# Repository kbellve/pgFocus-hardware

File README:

View this project on [CADLAB.io](https://cadlab.io/project/1071). 

pgFocus stands for Pretty Good Focus. It isn't "Definite" Focus nor "Perfect" Focus, but it is Pretty Good.  

pgFocus is fully compatible with uManager.

	1) Open Source Software

	2) Open Hardware

	3) Reasonably Fast
		pgFocus runs at 30Hz

	4) Reasonably inexpensive

	5) Independent of image capture
		In primary mode, pgFocus is asynchronous of uManager.

	6) uManager will be able to set, confirm or change focus positions through a uManager device adapter.

	7) Designed to work with a piezo Z controller for fastest response, but could be used to indirectly drive a motorized Z-Drive via a uManager device adapter.

	8) 3D Focus Stabilization
		Most focus stabilization devices turn off during 3D image capture, unlike pgFocus.

	9) Focus stability reporting
		You will quickly learn what disturbs your microscope and how to minimize those disturbances.

The pgFocus hardware, including all the files required to produce the hardware, is licensed under a Creative Commons Attribution-ShareAlike 4.0 International License.

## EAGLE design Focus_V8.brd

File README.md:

pgFocus
=======

Focus Stabilization

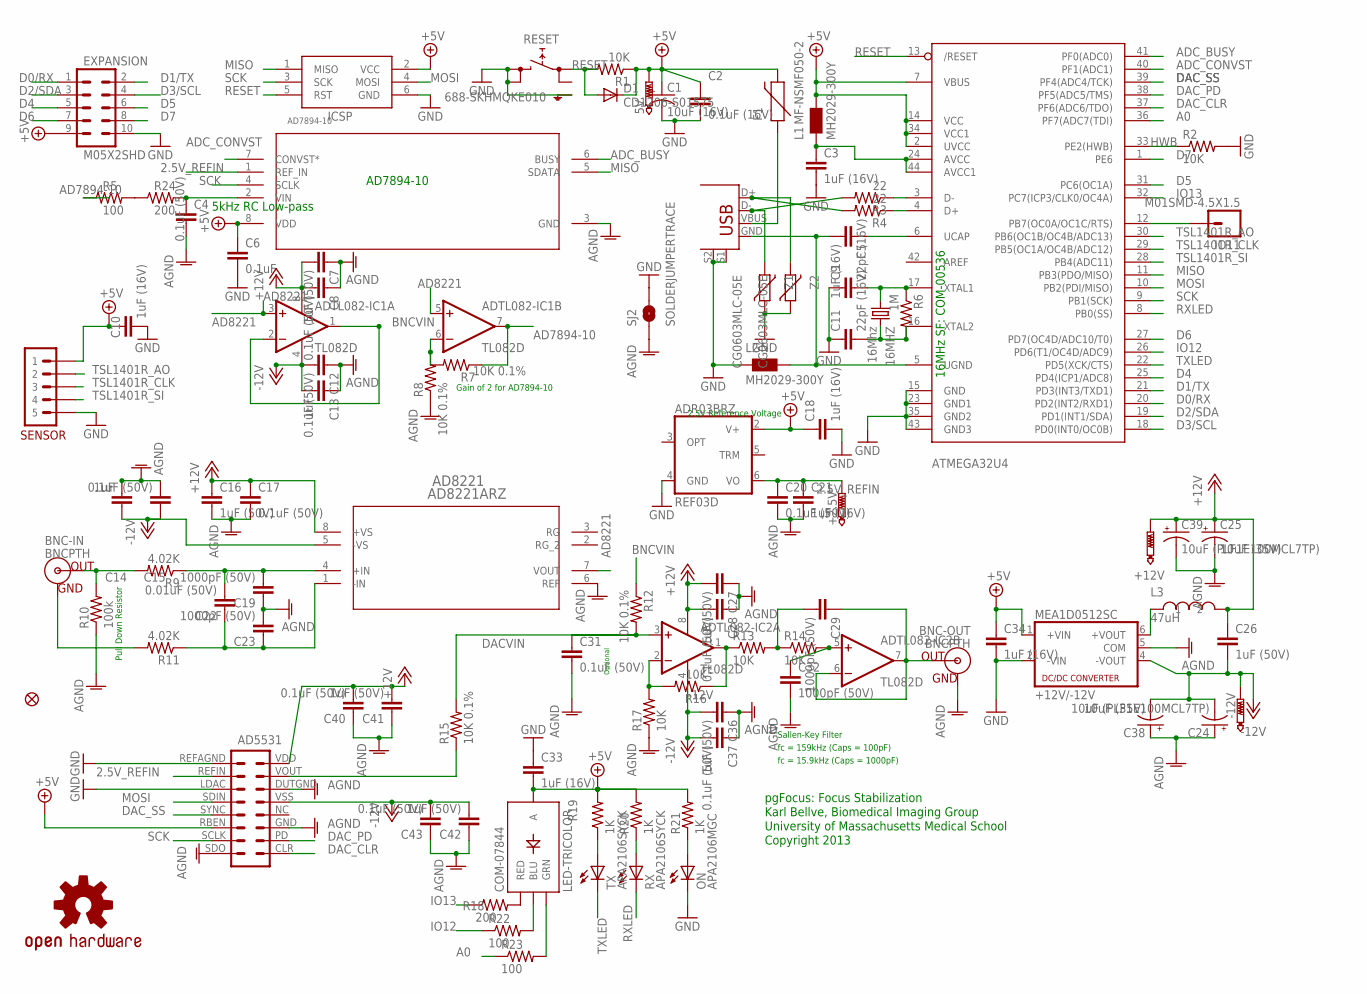
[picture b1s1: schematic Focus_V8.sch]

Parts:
5V: PTR1TP20R; TP20R
16MHZ: 16Mhz; HC49U-V
+2.5V, +12V: PTR1TP20R; TP20R
-12V: PTR1TP20R; TP20R
AD7894-10: AD7894ARZ-10; R_8
AD8221: AD8221ARZ; R_8
ADR03BRZ: REF03D; SO08
ADTL082-IC1, ADTL082-IC2: TL082D; SO08
ATMEGA32U4: ATMEGA32U4-AU; TQFP44
BNC-IN: BNCPTH; BNC
BNC-OUT: BNCPTH; BNC
C1: 10uF (16V); EIA3216-KIT
C2: 0.1uF (16V); 0603-CAP
C3, C5, C10, C18, C21, C33, C34: 1uF (16V); 0603-CAP
C4, C8, C12, C15, C17, C20, C28, C31, C37, C40, C43: 0.1uF (50V); 0603-CAP
C6: 0.1uF; 0603-CAP
C7, C16, C26, C27, C36, C41, C42: 1uF (50V); 0603-CAP
C9, C11: 22pF (16V); 0603-CAP
C13, C14: 1uF; 0603-CAP
C19, C23, C29, C32: 1000pF (50V); 0603-CAP
C22: 0.01uF (50V); 0603-CAP
C24, C39: 10uF (PLF1E100MCL7TP); CPOL-RADIAL-100UF-25V
C25, C38: 10uF (35V); EIA3216-KIT
COM-07844: LED-TRICOLOR; LED-TRICOLOR-SMD
D1: CD1206-S01575; MINIMELF
EXPANSION: M05X2SHD; 2X5-SHROUDED
F1: MF-NSMF050-2; PTC-1206
ICSP: AVRISP-6; AVRISP
IO11: M01SMD-4.5X1.5; PAD-1.5X4.5
JP1: FIDUCIAL1.5X3; FIDUCIAL-1.5X3
L1, L2: MH2029-300Y; 0805
L3: 47uH; 11R473C
MEA1D0512SC: +12V/-12V; NMA
ON: APA2106MGC; CHIPLED_0805
R1, R2, R13, R14, R16, R17: 10K; 0603-RES
R3, R4: 22; 0603-RES
R5, R22, R23: 100; 0603-RES
R6: 1M; 0603-RES
R7, R8, R12, R15: 10K 0.1%; 0603-RES
R9, R11: 4.02K; 0603-RES
R10: 100k; 0603-RES
R18, R24: 200; 0603-RES
R19, R20, R21: 1K; 0603-RES
RESET: 688-SKHMQKE010; SKHMPXE010
RX: APA2106SYCK; CHIPLED_0805
SENSOR: M05; M05JST-PTH
SJ2: SOLDERJUMPERTRACE; SJ_2S-TRACE
TX: APA2106SYCK; CHIPLED_0805
U$1: AD5531
U$3: OSHW-LOGOL; OSHW-LOGO-L
USB: USB+SHIELD; USB-B-PTH
Z1, Z2: CG0603MLC-05E; CT/CN0603

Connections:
2.5V_REFIN: +2.5V.TP, AD7894-10.1 (REF_IN), ADR03BRZ.6 (VO), C20.1, C21.1, U$1.REFIN
+5V: 5V.TP, AD7894-10.8 (VDD), ADR03BRZ.2 (V+), ATMEGA32U4.2 (UVCC), ATMEGA32U4.7 (VBUS), ATMEGA32U4.14 (VCC), ATMEGA32U4.34 (VCC1), C1.A (+), C2.1, C6.1, C10.1, C18.1, C33.2, C34.1, COM-07844.A, D1.C, EXPANSION.9, F1.2, ICSP.2 (VCC), L1.2, MEA1D0512SC.1 (+VIN), R1.1, R19.2, R20.2, R21.2, SENSOR.P$1 (1), U$1.RBEN
+12V: +12V.TP, AD8221.8 (+VS), ADTL082-IC1.8 (V+), ADTL082-IC2.8 (V+), C7.2, C8.2, C16.1, C17.1, C25.A (+), C26.1, C27.2, C28.2, C39.1 (+), C40.2, C41.2, L3.P$2 (2), U$1.VDD
-12V: -12V.TP, AD8221.5 (-VS), ADTL082-IC1.4 (V-), ADTL082-IC2.4 (V-), C12.2, C13.2, C14.1, C15.1, C24.2 (-), C26.2, C36.2, C37.2, C38.C (-), C42.2, C43.2, MEA1D0512SC.4 (-VOUT), U$1.VSS
A0: ATMEGA32U4.36 (PF7(ADC7(TDI)), R23.1
AD7894-10: ADTL082-IC1.7 (OUT), R5.1, R7.1
AD8221: AD8221.7 (VOUT), ADTL082-IC1.3 (+IN), ADTL082-IC1.5 (+IN)
ADC_BUSY: AD7894-10.6 (BUSY), ATMEGA32U4.41 (PF0(ADC0))
ADC_CONVST: AD7894-10.7 (CONVST*), ATMEGA32U4.40 (PF1(ADC1))
AGND: AD7894-10.3 (GND), AD8221.6 (REF), BNC-OUT.GND, C4.2, C7.1, C8.1, C12.1, C13.1, C14.2, C15.2, C16.2, C17.2, C19.1, C20.2, C21.2, C23.2, C24.1 (+), C25.C (-), C27.1, C28.1, C31.2, C32.2, C36.1, C37.1, C38.A (+), C39.2 (-), C40.1, C41.1, C42.1, C43.1, MEA1D0512SC.5 (COM), R8.1, R10.1, R17.1, SJ2.1, U$1.DUTGND, U$1.GND, U$1.SDO
BNCVIN: ADTL082-IC1.1 (OUT), ADTL082-IC1.2 (-IN), R12.1
D0/RX: ATMEGA32U4.20 (PD2(INT2/RXD1)), EXPANSION.1
D1/TX: ATMEGA32U4.21 (PD3(INT3/TXD1)), EXPANSION.2
D2/SDA: ATMEGA32U4.19 (PD1(INT1/SDA)), EXPANSION.3
D3/SCL: ATMEGA32U4.18 (PD0(INT0/OC0B)), EXPANSION.4
D4: ATMEGA32U4.25 (PD4(ICP1/ADC8)), EXPANSION.5
D5: ATMEGA32U4.31 (PC6(OC1A)), EXPANSION.6
D6: ATMEGA32U4.27 (PD7(OC4D/ADC10/T0)), EXPANSION.7
D7: ATMEGA32U4.1 (PE6), EXPANSION.8
DACVIN: ADTL082-IC2.3 (+IN), C31.1, R12.2, R15.2
DAC_CLR: ATMEGA32U4.37 (PF6(ADC6/TDO)), U$1.CLR
DAC_PD: ATMEGA32U4.38 (PF5(ADC5/TMS)), U$1.PD
DAC_SS: ATMEGA32U4.39 (PF4(ADC4/TCK)), U$1.SYNC
GND: ADR03BRZ.4 (GND), ATMEGA32U4.15 (GND), ATMEGA32U4.23 (GND1), ATMEGA32U4.35 (GND2), ATMEGA32U4.43 (GND3), C1.C (-), C2.2, C3.2, C6.2, C9.1, C10.2, C11.1, C18.2, C33.1, C34.2, EXPANSION.10, ICSP.6 (GND), L2.1, MEA1D0512SC.2 (-VIN), ON.CATHODE (C), R2.2, RESET.3 (2.1), RESET.4 (2.2), RESET.5 (SH), SENSOR.P$5 (5), SJ2.2, U$1.LDAC, U$1.REFAGND, USB.S1, USB.S2, Z1.1, Z2.1
HWB: ATMEGA32U4.33 (PE2(HWB)), R2.1
IO12: ATMEGA32U4.26 (PD6(T1/OC4D/ADC9)), R22.1
IO13: ATMEGA32U4.32 (PC7(ICP3/CLK0/OC4A)), R18.1
MISO: AD7894-10.5 (SDATA), ATMEGA32U4.11 (PB3(PDO/MISO)), ICSP.1 (MISO)
MOSI: ATMEGA32U4.10 (PB2(PDI/MISO)), ICSP.4 (MOSI), U$1.SDIN
unnamed: ADTL082-IC2.2 (-IN), R16.2, R17.2
unnamed: ADTL082-IC2.5 (+IN), C32.1, R14.2
unnamed: AD7894-10.2 (VIN), C4.1, R24.2
unnamed: AD8221.1 (-IN), C22.1, C23.1, R11.1
unnamed: R5.2, R24.1
unnamed: L3.P$1 (1), MEA1D0512SC.6 (+VOUT)
unnamed: ADTL082-IC2.1 (OUT), R13.1, R16.1
unnamed: R15.1, U$1.VOUT
unnamed: R19.1, TX.ANODE (A)
unnamed: ATMEGA32U4.4 (D+), R4.1
unnamed: 16MHZ.1, ATMEGA32U4.17 (XTAL1), C9.2, R6.1
unnamed: R20.1, RX.ANODE (A)
unnamed: BNC-IN.GND, R11.2
unnamed: AD8221.4 (+IN), C19.2, C22.2, R9.1
unnamed: ATMEGA32U4.6 (UCAP), C5.1
unnamed: C29.2, R13.2, R14.1
unnamed: BNC-IN.S (OUT), R9.2, R10.2
unnamed: ADTL082-IC1.6 (-IN), R7.2, R8.2
unnamed: R3.2, USB.D-, Z1.2
unnamed: ATMEGA32U4.3 (D-), R3.1
unnamed: R4.2, USB.D+, Z2.2
unnamed: F1.1, USB.VBUS
unnamed: ADTL082-IC2.6 (-IN), ADTL082-IC2.7 (OUT), BNC-OUT.S (OUT), C29.1
unnamed: ON.ANODE (A), R21.1
unnamed: ATMEGA32U4.24 (AVCC), ATMEGA32U4.44 (AVCC1), C3.1, L1.1
unnamed: 16MHZ.2, ATMEGA32U4.16 (XTAL2), C11.2, R6.2
unnamed: ATMEGA32U4.12 (PB7(OC0A/OC1C/RTS)), IO11.P$1
unnamed: COM-07844.R (RED), R18.2
unnamed: COM-07844.B (BLU), R22.2
unnamed: COM-07844.G (GRN), R23.2
RESET: ATMEGA32U4.13 (/RESET), D1.A, ICSP.5 (RST), R1.2, RESET.1 (1.1)
RXLED: ATMEGA32U4.8 (PB0(SS)), RX.CATHODE (C)
SCK: AD7894-10.4 (SCLK), ATMEGA32U4.9 (PB1(SCK)), ICSP.3 (SCK), U$1.SCLK
TSL1401R_AO: ATMEGA32U4.30 (PB6(OC1B/OC4B/ADC13)), SENSOR.P$2 (2)
TSL1401R_CLK: ATMEGA32U4.29 (PB5(OC1A/OC4B/ADC12)), SENSOR.P$3 (3)
TSL1401R_SI: ATMEGA32U4.28 (PB4(ADC11)), SENSOR.P$4 (4)
TXLED: ATMEGA32U4.22 (PD5(XCK/CTS)), TX.CATHODE (C)
UGND: ATMEGA32U4.5 (UGND), C5.2, L2.2, USB.GND

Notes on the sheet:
Pull Down Resistor
pgFocus: Focus Stabilization
2.5V Reference Voltage
16MHz SF: COM-00536
Sallen-Key Filter
fc = 159kHz (Caps = 100pF)
fc = 15.9kHz (Caps = 1000pF)
Karl Bellve, Biomedical Imaging Group
University of Massachusetts Medical School
Copyright 2013
AD7894-10
5kHz RC Low-pass
Gain of 2 for AD7894-10
Optional

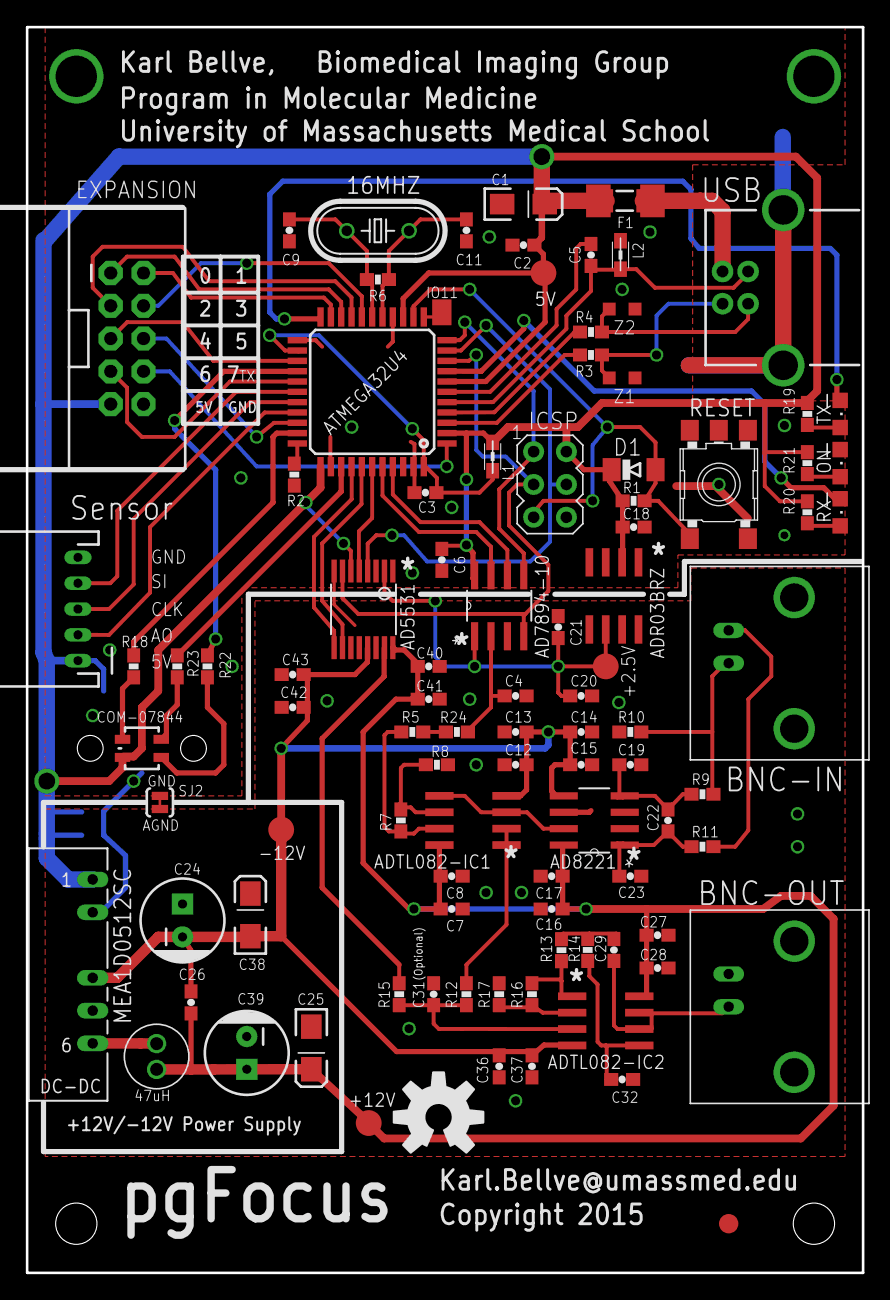
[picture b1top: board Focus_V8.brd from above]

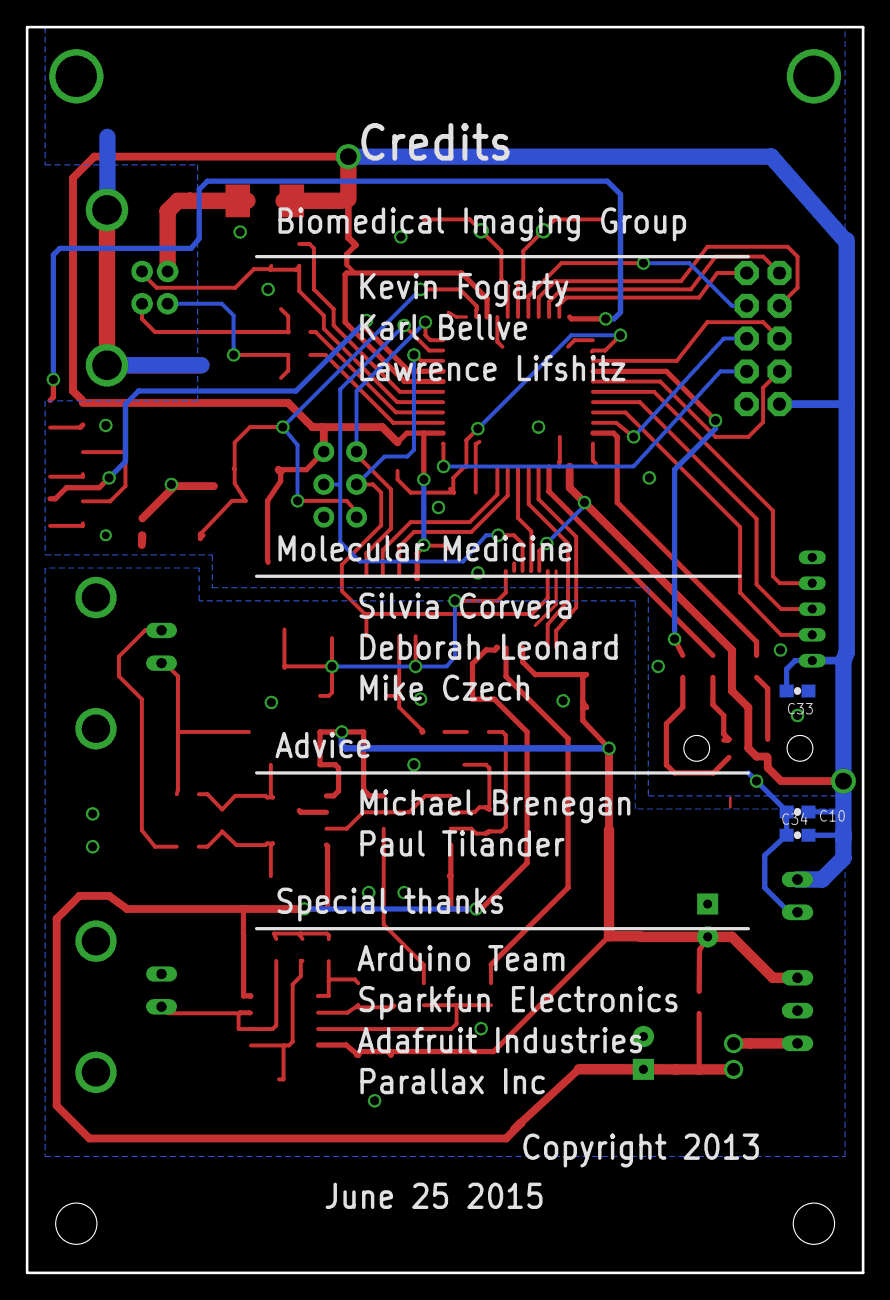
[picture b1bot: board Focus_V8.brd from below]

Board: 2 copper layers, 64.8 x 96.5 mm, 101 parts (3 on the bottom side), 67 nets.

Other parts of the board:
U$2: SMD-22

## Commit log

2013-02-19 Removing README.md
2013-02-19 Added eagle schematic and board files
2013-02-19 Description of board layout
2013-02-19 some editing
2013-02-20 Edited readme
2013-02-20 Adding PDF of top and bottom of board
2013-02-20 Top and Bottom of board
2013-02-22 Changed hole size from 1.6 to 2.2mm for TSL1401CL shroud
2013-02-27 Pin 7 of TC7660 has a capacitor labeled C35, which should have been connected to ground, and not 5V This has been corrected in this revision. C35 is optional, and not needed. Only use if trying to sl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
2013-03-11 LDAC pin of AD5531 needs to be tied to ground, Clean up of text
2013-04-05 Version 8 removes the Linear Light Array and uses a TSL1401CL-Adapter Board via a 5 pin JST SH connector. There is also a 3 pin JST connector for communicating with a Serial Enabled LCD display RGB L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
2013-04-05 Minor changes
2013-04-11 Changed connector for Expansion, cleaned up text
2013-04-24 Switchedd top two holes 1/8" Vias for mounting for chasis grounding
2013-05-01 Latest version sent to manufacturing
2013-09-20 Change connection between analog and digital ground plans via a cutable trace, which means that both ground planes will be connected by default.
    Also pin 6 (RBEN) of AD5531 was mistakenly left floating, now connected to 5V line to
    force deactivation.
2013-10-16 Removed V7 pgFocus
2015-06-29 Small changes to connectors on the rear edge of the main board. Reposition the sensor and expansion connector Removed the LCD connector Repositioned the RGB LED
2015-09-05 Added Gitter link
2015-12-01 Updating to eliminate serial LCD connector, and to make a horizontal expansion possible. This simplifies using a box to contain the PCB
2018-05-22 Backlink to CADLAB.io has been added.

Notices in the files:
Focus_V8.brd:
Copyright 2015
parts and their libraries:
SparkFun-Connectors: Licensing: CC v3.0 Share-Alike You are welcome to use this library for commercial purposes.
